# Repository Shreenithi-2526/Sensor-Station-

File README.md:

>>>

# Sensor Station 

by: 
Shreenithi Madhavan, 28639
_Mechatronic Systems Engineering_

Shreshth Khosla, 28644
_Electrical and Electronics Engineering_

**Faculty of Technology and Bionics**

***Rhine-Waal University of Applied Sciences***

Date: 09 January 2023   

----
## Acknowledgment 

We would like to thank our Project Supervisors for guiding us through this project and giving us prompt and quality feedback. We would also like to thank our seniors/student assistants for giving us good advice based on their experience. This project is solely written by the members of Group 10 and all the references used are documented in the report.

Kleve, 
09.01.2023

Shreenithi Madhavan

Shreshth Khosla 

## Abstract

The project aims to measure the surrounding weather conditions from the sensor and successfully transmit the data to the OLED display through a microcontroller.
The board gets powered by a lithium battery which gives an output of 3.3V, safeguarded by a battery management system. We can recharge the battery using a mini USB which turns on an orange LED indicating a successful connection.
The microcontroller chip is programmed using an FTDI module communicating through an I2C interface. After the chip is successfully programmed, the OLED should display the measured values.

## Table of contents

1. [Acknowledgement](#introduction)
2. [Abstract](#abstract)
3. [Table of Contents](#introduction)
4. [Introduction](#introduction)\
   4.1 [Background](#background)
8. [Theory](#introduction)
9. [Methodology](#introduction)
10. [Results](#introduction)
11. [Discussion](#introduction)
12. [Concluding Comments](#introduction)
13. [References](#introduction)

## Introduction

A Weather Sensor station is an environmental monitoring device/gadget used to gather information regarding the current temperature, pressure & humidity. It plays a vital role in providing governments, businesses, and individuals with the data they need to stay prepared and respond appropriately during weather challenges. A sensor station can range from a simple household device dedicated to measuring the surroundings data to a complex gadget that measures the weather conditions & also predicts the numbers for the future. Hence, a sensor station is an indispensable device. 

###	Background

After finalizing the project idea, the research about the components, sensors, and chips began. The aim while choosing the parts was to focus on the features, cost efficiency, and long-activity. 
We also focused on buying THT parts, attached to the board using female headers, to repurpose in the future.

The project is built on a PCB using an ESP32-WROOM-32D chip, DHT22, an external temperature & Humidity sensor, and an OLED to display the values gathered using the sensor. The idea can be leveled-up by providing the data directly to a Wifi/BlueTooth-enabled device as an application of IoT.    

| Component                 | Specification   |
|------------------------------|------------------------------|
| FTDI module                  | FT232-AZ    |
| OLED panel                   | 0.96", OLED Display, SSD1306  |
| Temperature/Humidity sensor  |	RHT03_DHT-22_AM2302  |
| Microcontroller	          | ESP32-WROOM-32D   |
| Pushbutton (x4)              |     |
| Resistor SMD (x3)10k	      | R1206W  |
| Resistor SMD 2k	          | R1206W |
| Resistor SMD 470	          | R1206W |
| Capacitor SMD (x2) 10uF	  | C-EUC1206 |
| Capacitor SMD (x2) 4.7uF	  | C-EUC1206 |
| Temperature/Humidity sensor  |	RHT03_DHT-22_AM2302  |
| 6 Pin Female Headers (x2)    |  - | 
| Pushbutton (x4)              | FT232-AZ    |
| 4 Pin Female Header          | -  |
| LDO Voltage Regulators       | AZ1117CH-3.3TRG1 |
| LED2	                      | LEDSMT1206 |
| USBMINIB                     | USB BWM SMD   |
| Battery Management Li-Ion    | MCP73831T-5ACI/OT  |
| Battery Connector            | JST PH2P STS |
| Battery 	                  | Li-Ion 3.7V 500mAh |

##	Theory

To understand how the PCB works, it is essential to be familiar with the working of some individual components. Brief explanantion of the parts is provided below:

•	**ESP 32-WROOM-32D**
This is the microcontroller used in our circuit. It is a powerful Wifi+Bluetooth MCU that can be used for a wide range of applications. The pin layout is provided below.

•	**DHT22 Sensor**
We have used the DHT 22 sensor, made of a capacitive humidity sensor and a thermistor. It consists of a chip that does analog to digital conversion to display the temperature and humidity with the help of a microcontroller. It is ideal for displaying 0-100% humidity readings with 2-5% accuracy and -40 to 80°C temperature readings with ±0.5°C accuracy.

The pin layout of the sensor is :

Vcc	- Power supply 3.5V to 5.5V

Data -	Outputs both Temperature and Humidity through serial Data

NC -	No Connection and hence not used

Ground -	Connected to the ground of the circuit

•	**OLED Display**
As the name indicates, it displays the measured data through I2C communication. It conducts electricity to organic materials which are sandwiched between the electrodes for light emission.

The pins used of the OLED display are:

SDA – Serial data pin for I2C interface

SCL – Serial clock pin for I2C interface

GND – Ground pin

VCC – power supply for display

•	**FTDI Module**
The FTDI module uses an FTDI chip that converts the USB signal to a UART (Universal asynchronous receiver-transmitter) signal for our microcontroller to understand. It, therefore, aids in programming the ESP32-WROOM-32D chip using Arduino IDE.
The programming process is automatic. It uses two switches, BC547 transistors, and other components.
The RTS signal is for resetting the ESP and the DTR signal is to put the chip in flashing mode.

The pins used in the FTDI module is :

GND- Ground pin

RX- Input data reception

TX- Output data transmission

Vcc- Input data reception

•	**Voltage Regulator**
AMS1117-3.3 is a cost-efficient, low dropout (LDO) Voltage Regulator designed to provide a current of up to 1 ampere. The output voltage can vary from 1.5V to 5V. It also has a low dropout voltage of 1.3V when operating at maximum current. The maximum input voltage it can support is 15V. This device is used to obtain a steady voltage of 3.3V from the power source.

The pin layout is as follows:

ADJ/GND- Ground pin

Vout- Regulated output voltage

Input- Input voltage that has to be regulated

•	**Battery Management**
We use MCP73831 IC to charge the battery. It is an advanced linear charge management controller which is compact and budget friendly as well. It adopts a constant current/constant voltage circuit to prevent overcharging.

The pins layout is :

Vdd- Battery management input supply

Vbat- Battery charge control output

STAT- Charge status output

PROG- Current regulation set & charge control enable

##  Methodology

**Hardware**

**Design**

The design phase started as soon as the part list was ready. 

Initially, we intended to use the ESP32 Developer kit. But, since it was not allowed, we decided to use the raw chip. We researched to find a suitable method for programming. Accordingly, we designed our circuit and decided to use an FTDI module for programming the chip on Arduino IDE.

We started with the schematic design on Autodesk Eagle. The process took a couple of revisions to finalize the circuit design as we had to search the libraries and manually add them to Eagle according to the component requirements. We also did the ERC check where we had to rectify errors in the schematic.

After successfully eradicating and approving the errors in the schematic, we moved to the next task of building the board view using the schematic layout. While working with the board view, we spaced out the components far enough from each other to avoid congestion and ease the process while soldering. We also had to follow some steps/rules while designing the board view to manufacture the PCB in-house without any issues. We removed the DRC errors from the board view design.

**Manufacturing the PCB** 

•	**Printing** - We printed the board view design on a laminated plastic A4 sheet with the bottom and top layers mirrored to each other on the ends of the sheet.

•	**Cutting** - A board with copper plating is cut to the desired dimensions of the printout using a cutting machine for precision.

•	**PCB Masking** - The printed laminated is placed on the board for UV exposure.

•	**Uv exposure** - This board is placed under UV light for 2:30 minutes.

•	**Developing**- The board is placed in a solution of sodium hydroxide

•	**Etching**- The PCB is etched using iron chloride to get rid of the unprotected copper.

•	**Cleaning**- The PCB is wiped with alcohol to remove unwanted residue.

•	**Drilling** - After checking the connections between the tracks, we drilled holes for the THT components & the VIAS. It is used to connect the top & the bottom layer. The VIAS were punched down using a punching machine.

•	**Placing & Soldering** - Lastly, after successfully drilling the holes, we moved to the final step of soldering & mounting. We tried to put the SMD paste as precisely as possible to avoid spreading over other pads. We used the Pick and place machine to mount the SMD components of the PCB. The board with the components was put in the oven for 20 minutes to stick the parts firmly. Finally, we soldered the THT components after the previous task. 

After manufacturing the PCB, we realized that the connection from 10uF capacitor via voltage regulator to the power supply was incomplete. We tackled this problem by soldering a wire to complete the connection.

The placement of the mini-USB port was such that the cable for recharging the battery could not fit in the port. So, we cut the board such that the cable fits inside the port.

**Software**

The Coding part has been attached below

```
#include <Wire.h>
#include <Adafruit_GFX.h>
#include <Adafruit_SSD1306.h>
#include <Adafruit_Sensor.h>
#include <DHT.h>

#define SCREEN_WIDTH 128 // OLED display width, in pixels
#define SCREEN_HEIGHT 64 // OLED display height, in pixels
Adafruit_SSD1306 display(SCREEN_WIDTH, SCREEN_HEIGHT, &Wire, -1);

#define DHTPIN 19     // Digital pin connected to the DHT sensor

// Uncomment the type of sensor in use:
//#define DHTTYPE    DHT11     // DHT 11
#define DHTTYPE    DHT22     // DHT 22 (AM2302)
//#define DHTTYPE    DHT21     // DHT 21 (AM2301)
DHT dht(DHTPIN, DHTTYPE);

void setup() {
  Serial.begin(115200);

  dht.begin();

  if(!display.begin(SSD1306_SWITCHCAPVCC, 0x3C)) {
    Serial.println(F("SSD1306 allocation failed"));
    for(;;);
  }
  delay(2000);
  display.clearDisplay();
  display.setTextColor(WHITE);
}

void loop() {
  delay(5000);

  //read temperature and humidity
  float t = dht.readTemperature();
  float h = dht.readHumidity();
  if (isnan(h) || isnan(t)) {
    Serial.println("Failed to read from DHT sensor!");
  }
  // clear display
  display.clearDisplay();
  
  // display temperature
  display.setTextSize(1);
  display.setCursor(0,0);
  display.print("Temperature: ");
  display.setTextSize(2);
  display.setCursor(0,10);
  display.print(t);
  display.print(" ");
  display.setTextSize(1);
  display.cp437(true);
  display.write(167);
  display.setTextSize(2);
  display.print("C");
  
  // display humidity
  display.setTextSize(1);
  display.setCursor(0, 35);
  display.print("Humidity: ");
  display.setTextSize(2);
  display.setCursor(0, 45);
  display.print(h);
  display.print(" %"); 
  
  display.display(); 
}

```

## Results

The outcome of the printed circuit board should look like this. 

##	Discussion

 After uploading the code to the microcontroller, the DHT 22 sensor measures the data (Temperature and humidity) from the surroundings and displays it on the OLED panel.
 
 Attached below is a picture of the prototyping of the sensor station.

##	Concluding Comments

As a next step to our project, this sensor station could be advanced to an IoT project. The values would be displayed directly to a device with Wifi/Bluetooth enabled by programming the code accordingly. We wish to make use of our board to the fullest. For the same reason, we have added six extra GPIOs for future expansion.

##	References

* [1] https://www.mischianti.org/2021/05/26/esp32-wroom-32-high-resolution-pinout-and-specs/
* [2] https://learn.adafruit.com/dht
* [3] https://lastminuteengineers.com/oled-display-arduino-tutorial/
* [4] https://randomnerdtutorials.com/esp32-weather-station-pcb/
* [5] https://how2electronics.com/design-your-own-esp-board-for-battery-powered-iot-applications/
* [6] https://www.studiopieters.nl/esp32-program-a-esp32/
* [7] https://randomnerdtutorials.com/esp32-dht11-dht22-temperature-humidity-sensor-arduino-ide/
* [8] https://controls.hsrw.org/dokuwiki/doku.php?id=ee:pcbfoametching
* [9]	https://www.ourpcb.com/ftdi-pinout.html

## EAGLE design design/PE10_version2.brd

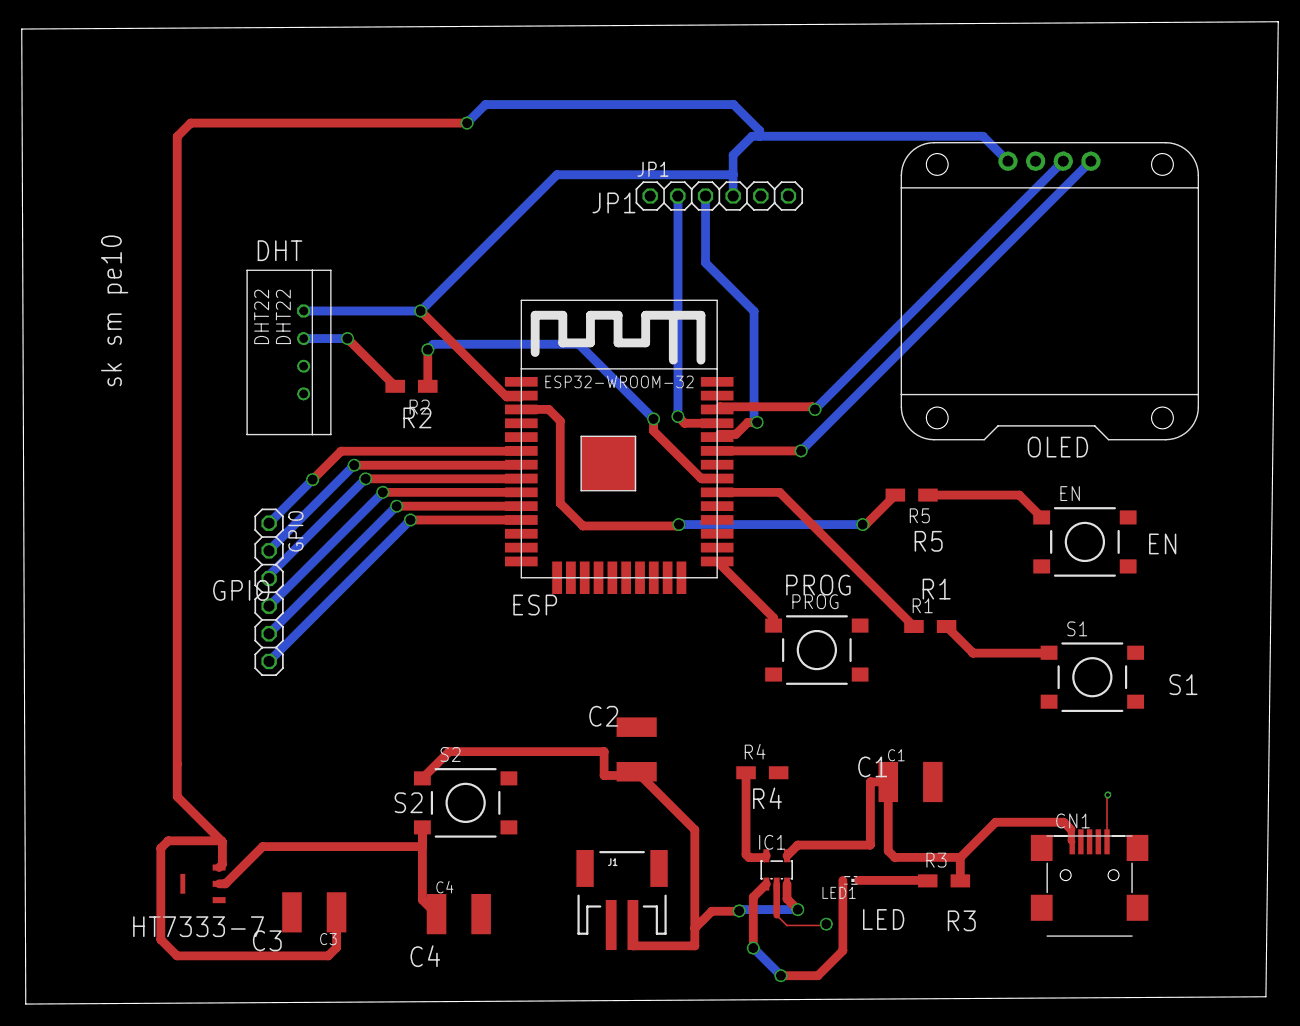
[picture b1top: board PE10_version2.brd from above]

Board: 2 copper layers, 115.5 x 90.3 mm, 23 parts (0 on the bottom side), 25 nets.

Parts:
C1: 4.7UF; C1812K
C2: 4.7uF; C1812K
C3, C4: 10uF; C1812K
CN1: CN1; USB-MINIB
DHT22: DHT22; RHT03_DHT-22
EN: DTSM-6
GPIO: 1X06
HT7333-7: HT7333; SOT89
IC1: MCP73831/OT; SOT23-5L
J1: 5V; JST-2-SMD
JP1: JP1; 1X06
LED1: RED; SMART-LED
OLED0.96: OLED_0.96_I2C
PROG: DTSM-6
R1, R2, R5: 10k; R1206W
R3: 470; R1206W
R4: 2K; R1206W
S1, S2: DTSM-6
U$1: ESP32-WROOM

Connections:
0: C1.2, C2.2, C3.2, C4.2, CN1.GND, DHT22.GND, EN.3, HT7333-7.GND, IC1.2, J1.1, JP1.6, OLED0.96.GND, PROG.3, R4.2, S1.3, U$1.GND1, U$1.GND2, U$1.GND3, U$1.GND4, U$1.GND5
3V3: C3.1, DHT22.VDD, HT7333-7.VOUT, JP1.4, OLED0.96.VCC, U$1.3V3
18: R1.1, U$1.IO18
19: R2.1, U$1.IO19
GPIO1: GPIO.1, U$1.IO34
GPIO2: GPIO.2, U$1.IO35
GPIO3: GPIO.3, U$1.IO32
GPIO4: GPIO.4, U$1.IO33
GPIO5: GPIO.5, U$1.IO25
GPIO6: GPIO.6, U$1.IO26
unnamed: OLED0.96.SCL, U$1.IO22
unnamed: OLED0.96.SDA, U$1.IO21
unnamed: DHT22.DATA, R2.2
unnamed: R1.2, S1.1
unnamed: C1.1, CN1.VBUS, IC1.4, R3.2
unnamed: C4.1, HT7333-7.VIN, S2.3
unnamed: IC1.1, LED1.A
unnamed: C2.1, IC1.3, J1.2, S2.1
unnamed: LED1.B, R3.1
unnamed: EN.1, R5.1
unnamed: IC1.5, R4.1
unnamed: R5.2, U$1.EN
PROG: PROG.1, U$1.IO0
RX: JP1.2, U$1.TX
TX: JP1.3, U$1.RX

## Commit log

2022-11-03 Upload New File

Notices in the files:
parts and their libraries:
SparkFun-Connectors: Licensing: Creative Commons ShareAlike 4.0 International - https://creativecommons.org/licenses/by-sa/4.0
